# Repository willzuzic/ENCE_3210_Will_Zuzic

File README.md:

# ENCE_3210_Will_Zuzic
Microprocessor Systems I

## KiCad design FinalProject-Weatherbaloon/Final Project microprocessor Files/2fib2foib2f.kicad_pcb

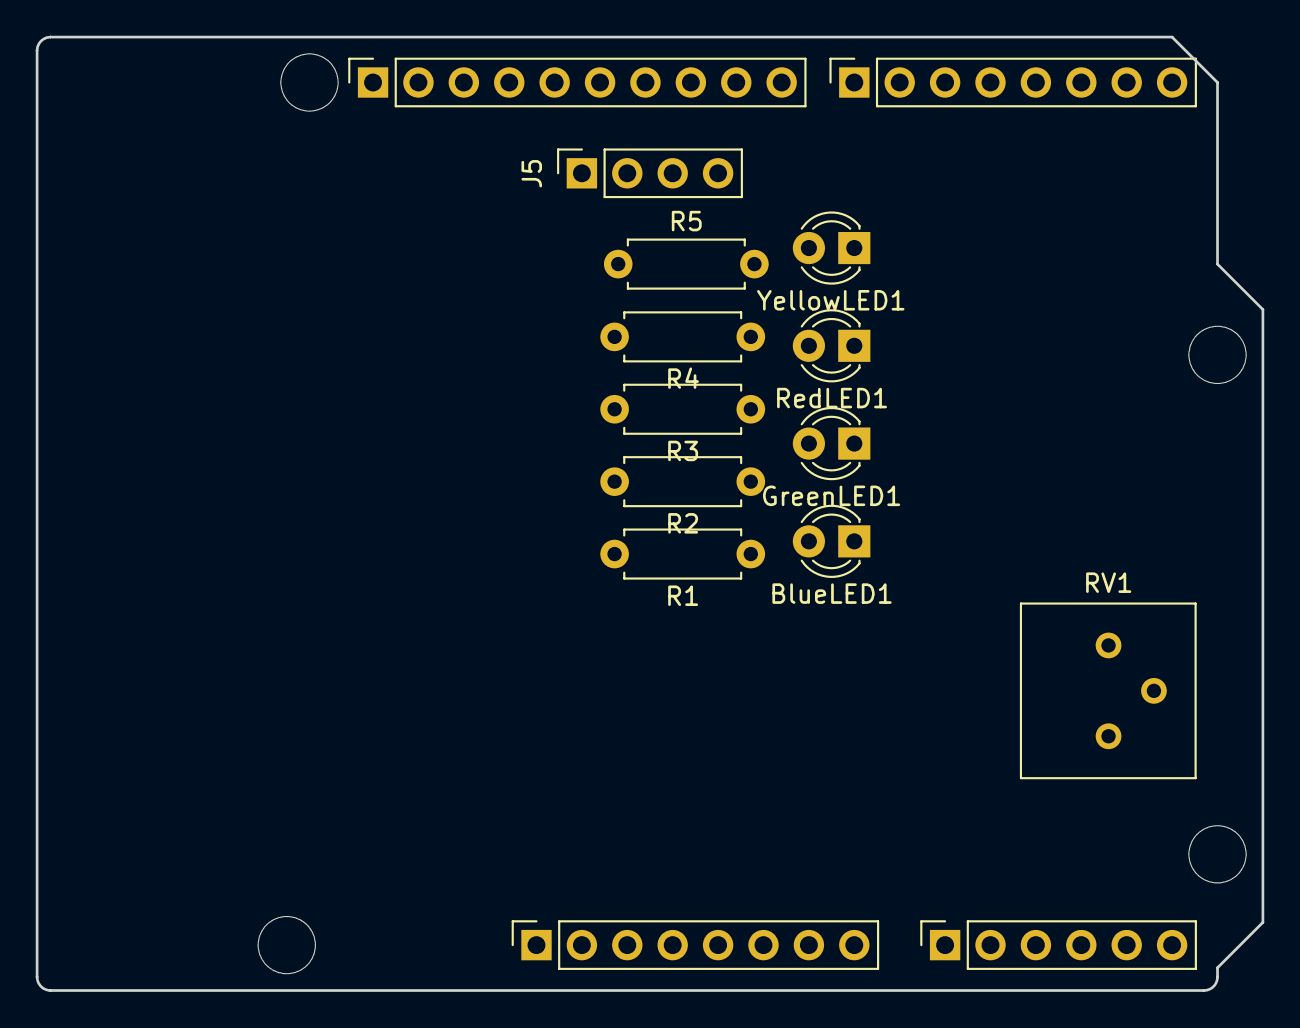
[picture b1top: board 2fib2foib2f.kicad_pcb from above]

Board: 2 copper layers, 68.6 x 53.3 mm, 19 parts (0 on the bottom side), 13 nets, no tracks yet.

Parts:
BlueLED1: LED; LED_D3.0mm
GreenLED1: LED; LED_D3.0mm
J1: Power; PinSocket_1x08_P2.54mm_Vertical
J2: Digital/PWM; PinSocket_1x10_P2.54mm_Vertical
J3: Analog; PinSocket_1x06_P2.54mm_Vertical
J4: Digital/PWM; PinSocket_1x08_P2.54mm_Vertical
J5: Temperature + Humidity Sensor; PinSocket_1x04_P2.54mm_Vertical
MH1, MH2, MH3, MH4: MountingHole_3.2mm
R1, R2, R3, R4: 330; R_Axial_DIN0207_L6.3mm_D2.5mm_P7.62mm_Horizontal
R5: 10k; R_Axial_DIN0207_L6.3mm_D2.5mm_P7.62mm_Horizontal
RV1: R_Potentiometer; Potentiometer_Bourns_3386P_Vertical
RedLED1: LED; LED_D3.0mm
YellowLED1: LED; LED_D3.0mm

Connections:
+5V: J1.5, J5.1, R5.1, RV1.1
/7: J4.1, R2.2
/*5: J4.3, R4.2
/*6: J4.2, R3.2
/*9: J2.9, R1.2
/A0: J3.1, J5.2, R5.2
/SCL/A5: J2.1, J3.6
/SDA/A4: J2.2, J3.5
GND: BlueLED1.1 (K), GreenLED1.1 (K), J1.6, J1.7, J2.4, J5.4, RV1.3, RedLED1.1 (K), YellowLED1.1 (K)
unnamed: BlueLED1.2 (A), R3.1
unnamed: GreenLED1.2 (A), R4.1
unnamed: R2.1, RedLED1.2 (A)
unnamed: R1.1, YellowLED1.2 (A)

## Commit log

2025-01-17 hopefully this works
2025-01-17 Adding folder hopefully
2025-01-17 wd1d1dxz
2025-01-17 Hopefully adding Lab1 with a folder
2025-01-17 Adding Lab2 Question 1 File
2025-01-17 Adding Question 2
2025-01-20 Adding more files
2025-01-20 adding to Lab1
2025-01-20 adding files
2025-01-22 Adding question2 to lab2
2025-02-04 Adding Proj Files
2025-02-25 af2uin
2025-02-26 sqdq
2025-02-28 iboih
2025-03-05 Liengn2piubug
2025-03-05 f2ef2f
2025-03-14 Adding Final Proj Files
2025-03-14 Adding Proj Files maybe
2025-03-14 adding presentation
2025-03-19 V2 of mass/price/ power/code
